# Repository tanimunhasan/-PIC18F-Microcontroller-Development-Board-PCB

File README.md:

# -PIC18F-Microcontroller-Development-Board-PCB

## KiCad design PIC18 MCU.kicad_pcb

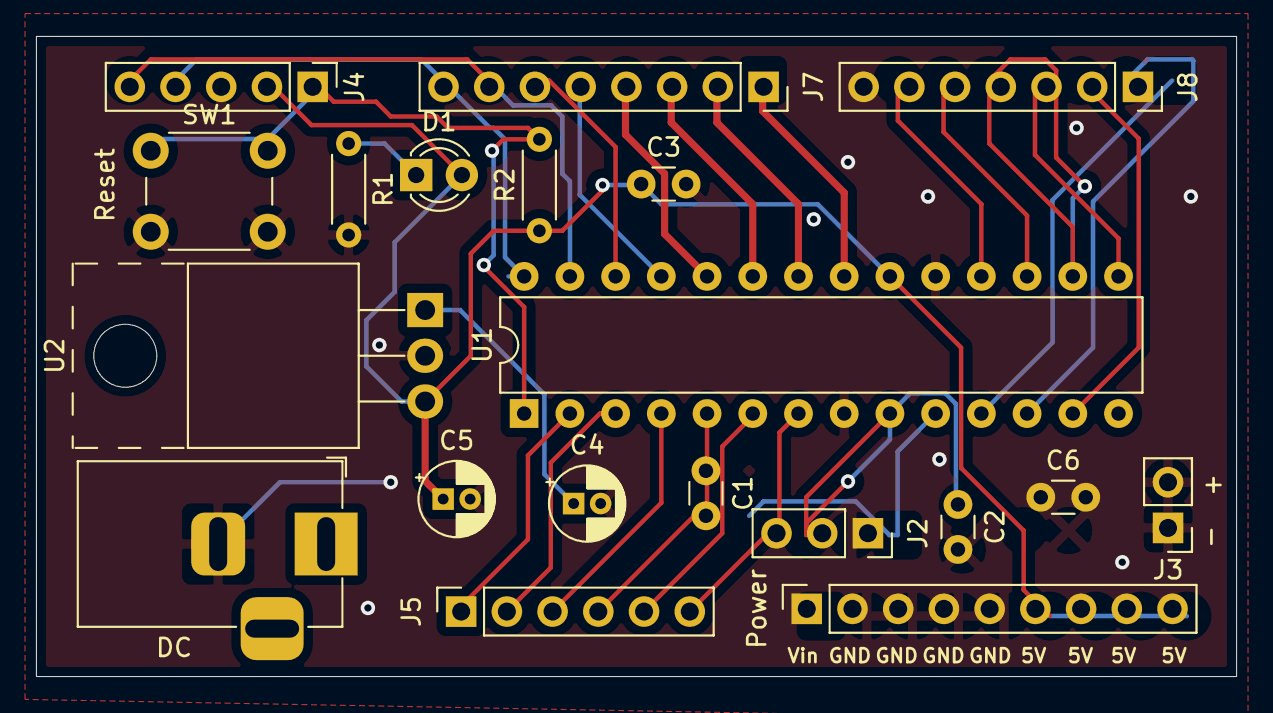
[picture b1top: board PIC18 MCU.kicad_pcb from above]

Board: 2 copper layers, 66.7 x 35.6 mm, 20 parts (0 on the bottom side), 28 nets.

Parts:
C1, C2: 22pF; C_Disc_D3.0mm_W1.6mm_P2.50mm
C3, C6: 100nF; C_Disc_D3.0mm_W1.6mm_P2.50mm
C4: 100uF; CP_Radial_D4.0mm_P1.50mm
C5: 1uF; CP_Radial_D4.0mm_P1.50mm
D1: LED; LED_D3.0mm
DC: DC; BarrelJack_Horizontal
J2: OSC; PinSocket_1x03_P2.54mm_Vertical
J3: GND Hook; PinHeader_1x02_P2.54mm_Vertical
J4: ICSP; PinHeader_1x05_P2.54mm_Vertical
J5: PORT A; PinSocket_1x06_P2.54mm_Vertical
J7: PORT B; PinSocket_1x08_P2.54mm_Vertical
J8: PORT C; PinSocket_1x07_P2.54mm_Vertical
Power: POWER PORT; PinSocket_1x09_P2.54mm_Vertical
R1, R2: R_Small; R_Axial_DIN0204_L3.6mm_D1.6mm_P5.08mm_Horizontal
SW1: SW_Push; SW_PUSH_6mm
U1: PIC18F2550-ISP; DIP-28_W7.62mm
U2: L7805; TO-220-3_Horizontal_TabUp

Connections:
+5V: C3.1, C5.1, C6.1, D1.2, J4.2, Power.6, Power.7, Power.8, Power.9, R2.1, U1.20, U2.3
GND: C1.1, C2.2, C3.2, C4.2, C5.2, C6.2, DC.2, J2.2, J3.1, J3.2, J4.3, Power.2, Power.3, Power.4, Power.5, R1.2, SW1.2, U1.8, U1.19, U2.2
MCLR: J4.1, R2.2, SW1.1, U1.1
unnamed: D1.1, R1.1
OSC1: C2.1, J2.3, U1.9
OSC2: C1.2, J2.1, U1.10
RA0: J5.1, U1.2
RA1: J5.2, U1.3
RA2: J5.3, U1.4
RA3: J5.4, U1.5
RA4: J5.5, U1.6
RA5: J5.6, U1.7
RB1: J7.2, U1.22
RB2: J7.3, U1.23
RB3: J7.4, U1.24
RB4: J7.5, U1.25
RB5: J7.6, U1.26
RB6: J4.5, J7.7, U1.27
RB7: J4.4, J7.8, U1.28
RBO: J7.1, U1.21
RC0: J8.1, U1.11
RC1: J8.2, U1.12
RC2: J8.3, U1.13
RC4: J8.4, U1.15
RC5: J8.5, U1.16
RC6: J8.6, U1.17
RC7: J8.7, U1.18
VIN: C4.1, U2.1
